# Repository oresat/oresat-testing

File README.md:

# oresat-testing
A place for all aspects of OreSat CubeSat testing

### Environmental

* Temperature (70 K to 350K) ??
* Vacuum (10ee-8 Torr)
* Vibration
* RF anechoic chamber

### RF Test equipment

* 10 MHz Rubidium Oscillator Standard
* GPS Disciplined Oscillator Standard
* Noise Source

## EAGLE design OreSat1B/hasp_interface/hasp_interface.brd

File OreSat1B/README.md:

# OreSat1B
OreSat1B is the HASP Balloon Test Payload of OreSat Subsystems to be flown on the HASP 2020 Payload round in Ft. Sumner, New Mexico.

### Tested Subsystems
- Cirrus Flux Camera
- OreSat Live
- Startracker
- C3 (Flight Computer)
- DxWiFi w/ Turnstile Antenna
- Handheld Ground Station

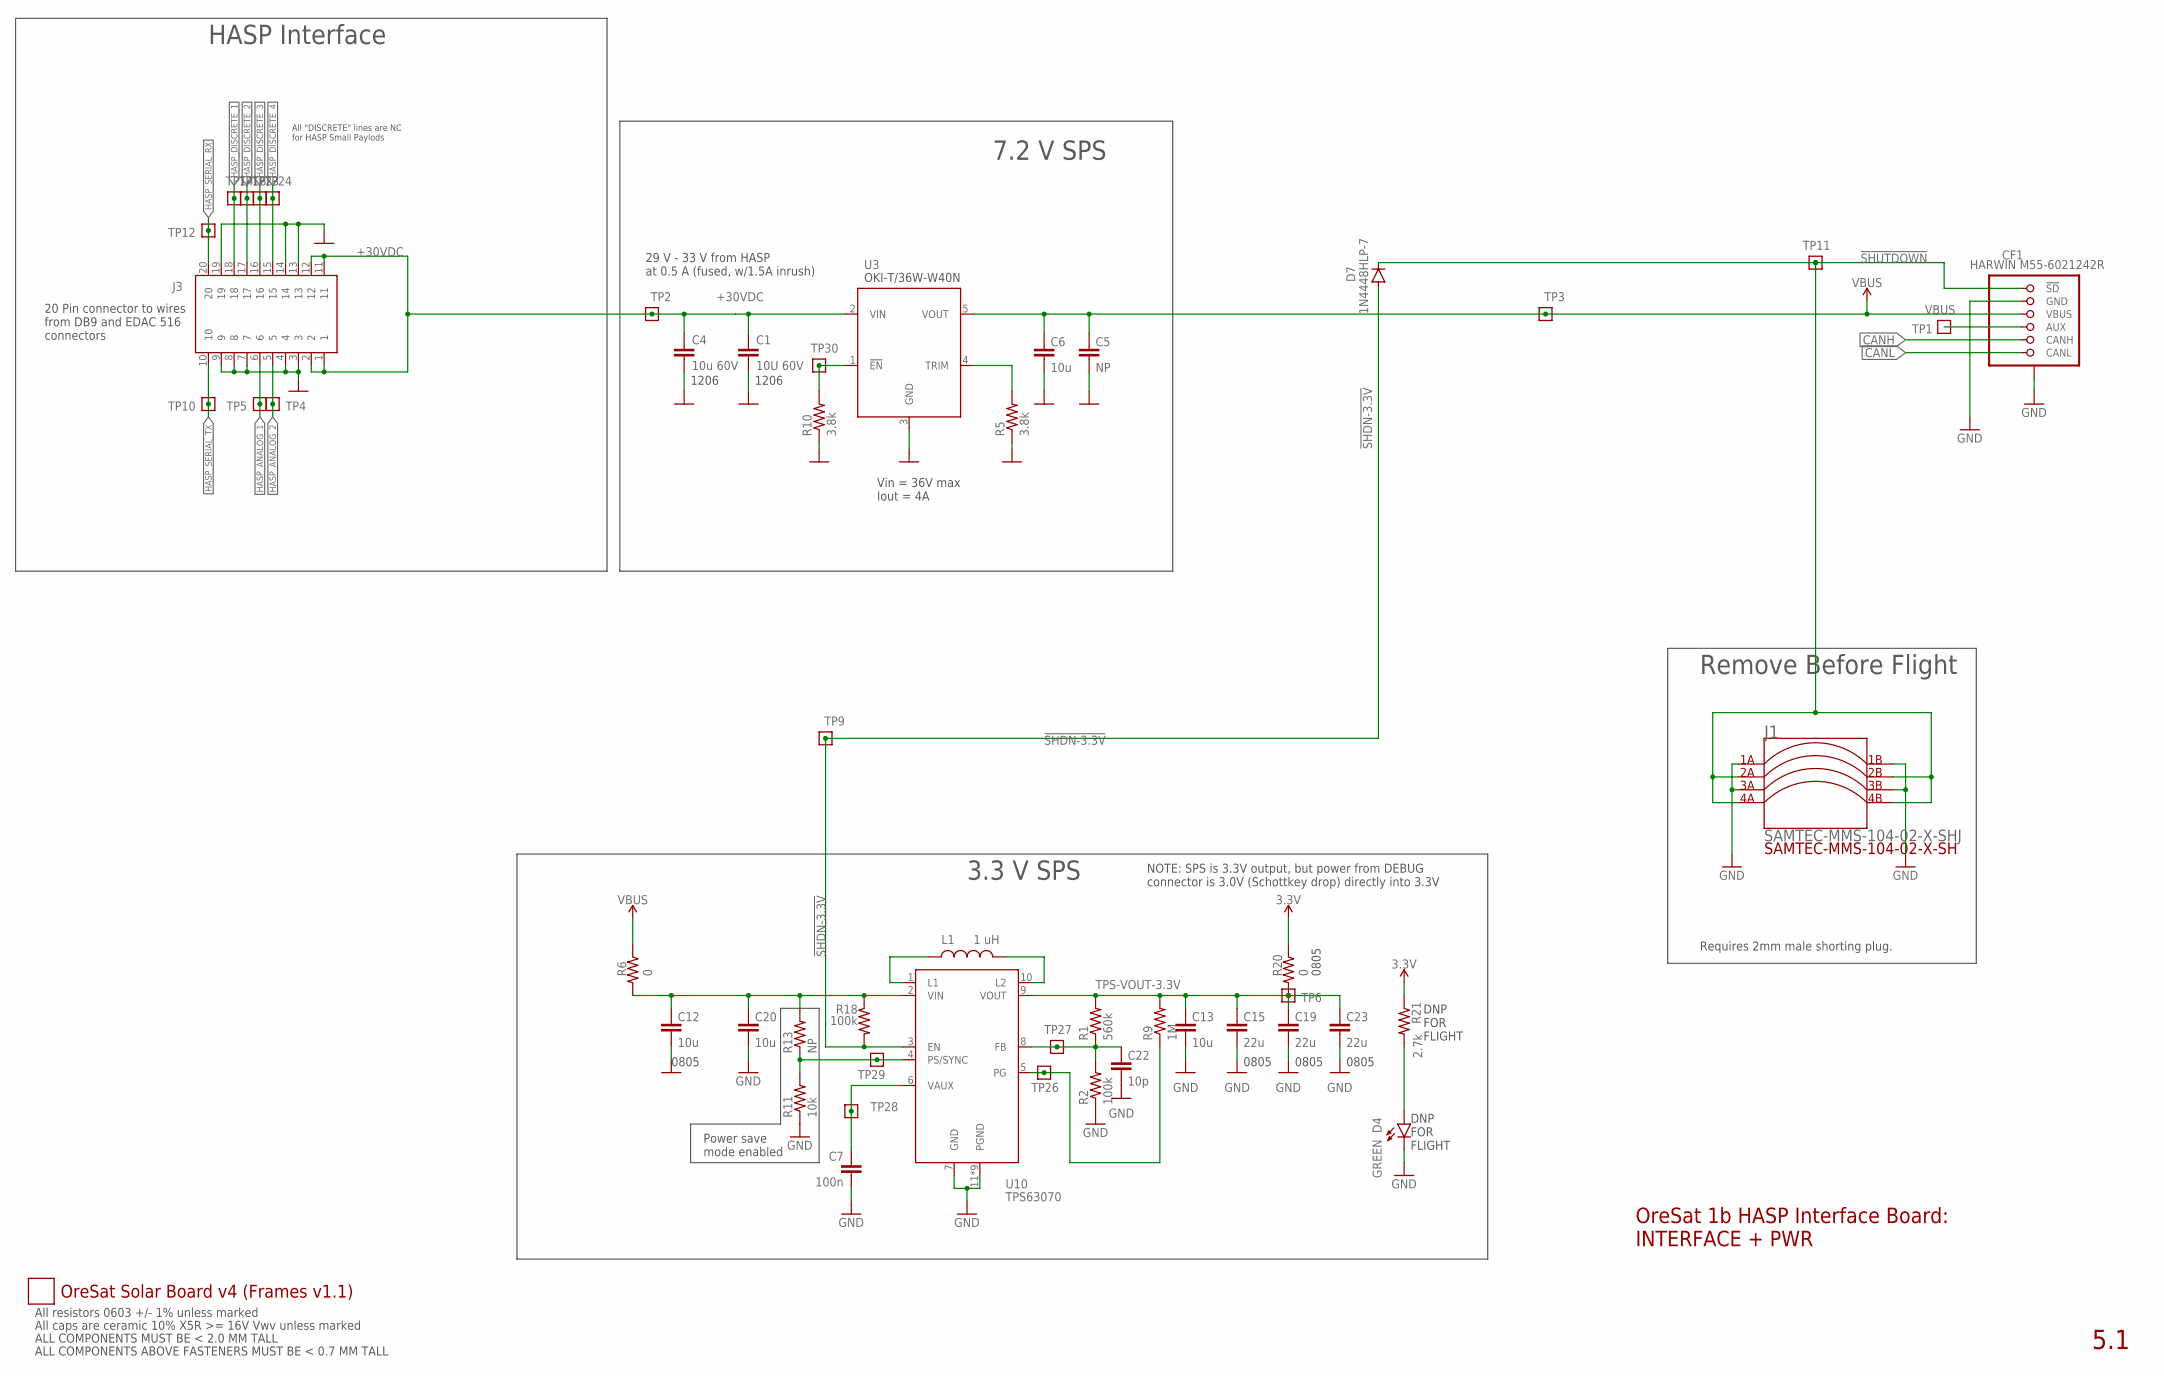
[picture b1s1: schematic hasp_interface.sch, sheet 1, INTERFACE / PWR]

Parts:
C1: 10U 60V; 1206-C
C4: 10u 60V; 1206-C
C5: NP; .0603-C-NOSILK; MPN GRT188R61C106KE13D
C6, C13, C20: 10u; .0603-C-NOSILK; MPN GRT188R61C106KE13D
C7: 100n; .0603-C-NOSILK; MPN CL10B104KB85PND
C12: 10u; .0805-B-NOSILK; MPN GRT21BR61C106KE01L
C15, C19, C23: 22u; .0805-B-NOSILK; MPN CL32B226KOJVPNE
C22: 10p; .0603-C-NOSILK; MPN GRT188R61C106KE13D
CF1: HARWIN M55-6021242R; HARWIN-M55-60X1242R
D4: GREEN; LED-0603; MPN IN-S63AT5A
D7: 1N4448HLP-7; .0402-B-NOSILK-DIODE; MPN 1N4448HLP-7
J1: SAMTEC-MMS-104-02-X-SHJ; SAMTEC-MMS-104-02-X-SH
J3: MOLEX-43045XXXXRIGHTANGLE; 0430452000
L1: 1 uH; IND_1226AS-H-1R0N=P2; MPN VLS3010CX-1R5M-1
PCB1: ORESAT-SOLAR-BOARD-V4-SPECTROLABS; ORESAT-SOLAR-BOARD-V4
R1: 560k; .0603-C-NOSILK; MPN CRGCQ0603F470K
R2: 100k; .0603-C-NOSILK; MPN RR0816P-104-D
R5, R10: 3.8k; .0603-C-NOSILK
R6, R20: 0; .0805-C-NOSILK; MPN RMCF0805ZT0R00
R9: 1M; .0603-C-NOSILK
R11: 10k; .0603-C-NOSILK
R13: NP; .0603-C-NOSILK; MPN RNCP0603FTD10K0
R18: 100k; .0603-C-NOSILK; MPN RNCP0603FTD10K0
R21: 2.7k; .0603-C-NOSILK; MPN CRGCQ0603F2K7
TP1, TP2, TP3, TP4, TP5, TP6, TP9, TP10, TP11, TP12, TP14, TP16, TP23, TP24, TP26, TP27, TP28, TP29, TP30: TEST-POINT-LARGE-SQUARE; 1X01
U3: OKI-T/36W-W40N; OKI-T/36W-W40
U10: TPS63070; CONV_TPS63060DSCT; MPN TPS63070RNMT

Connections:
3.3V: R20.1, R21.1; also elsewhere on the board
!SHDN-3.3V: D7.A, R18.2, TP9.1, U10.3 (EN)
!SHUTDOWN: CF1.1 (!SD), CF1.2 (!SD), D7.C, J1.2A, J1.2B, J1.4A, J1.4B, TP11.1
+30VDC: C1.1, C4.1, J3.1, J3.2, J3.11, J3.12, TP2.1, U3.2 (VIN)
AUX: CF1.7 (AUX), CF1.8 (AUX), TP1.1
CANH: CF1.9 (CANH), CF1.10 (CANH); also elsewhere on the board
CANL: CF1.11 (CANL), CF1.12 (CANL); also elsewhere on the board
GND: C1.2, C4.2, C5.2, C6.2, C7.2, C12.2, C13.2, C15.2, C19.2, C20.2, C22.2, C23.2, CF1.3 (GND), CF1.4 (GND), CF1.P$1 (SHIELD), CF1.P$2 (SHIELD), CF1.P$3 (SHIELD), CF1.P$4 (SHIELD), D4.C, J1.1A, J1.1B, J1.3A, J1.3B, J3.3, J3.4, J3.7, J3.8, J3.9, J3.13, J3.14, J3.19, R2.1, R5.1, R10.1, R11.1, U3.3 (GND), U10.7 (GND), U10.11 (PGND), U10.12 (PGND), U10.13 (PGND), U10.14 (PGND), U10.15 (PGND), U10.16 (PGND), U10.17 (PGND), U10.18 (PGND), U10.19 (PGND); also elsewhere on the board
HASP_ANALOG_1: J3.6, TP5.1; also elsewhere on the board
HASP_ANALOG_2: J3.5, TP4.1; also elsewhere on the board
HASP_DISCRETE_1: J3.18, TP14.1
HASP_DISCRETE_2: J3.17, TP16.1
HASP_DISCRETE_3: J3.16, TP23.1
HASP_DISCRETE_4: J3.15, TP24.1
HASP_SERIAL_RX: J3.20, TP12.1; also elsewhere on the board
HASP_SERIAL_TX: J3.10, TP10.1; also elsewhere on the board
unnamed: R5.2, U3.4 (TRIM)
unnamed: R10.2, TP30.1, U3.1 (!EN)
unnamed: D4.A, R21.2
TPS-EN: R11.2, R13.1, TP29.1, U10.4 (PS/SYNC)
TPS-FB: C22.1, R1.1, R2.2, TP27.1, U10.8 (FB)
TPS-L1: L1.1, U10.1 (L1)
TPS-L2: L1.2, U10.10 (L2)
TPS-PG: R9.1, TP26.1, U10.5 (PG)
TPS-VAUX: C7.1, TP28.1, U10.6 (VAUX)
TPS-VIN: C12.1, C20.1, R6.2, R13.2, R18.1, U10.2 (VIN)
TPS-VOUT-3.3V: C13.1, C15.1, C19.1, C23.1, R1.2, R9.2, R20.2, TP6.1, U10.9 (VOUT)
VBUS: C5.1, C6.1, CF1.5 (VBUS), CF1.6 (VBUS), R6.1, TP3.1, U3.5 (VOUT)

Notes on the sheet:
OreSat 1b HASP Interface Board: INTERFACE + PWR
5.1
All resistors 0603 +/- 1% unless marked
All caps are ceramic 10% X5R >= 16V Vwv unless marked
0805
3.3 V SPS
ALL COMPONENTS MUST BE < 2.0 MM TALL
ALL COMPONENTS ABOVE FASTENERS MUST BE < 0.7 MM TALL
NOTE: SPS is 3.3V output, but power from DEBUG connector is 3.0V (Schottkey drop) directly into 3.3V
Remove Before Flight
Requires 2mm male shorting plug.
DNP FOR FLIGHT
Power save mode enabled
HASP Interface
7.2 V SPS
29 V - 33 V from HASP at 0.5 A (fused, w/1.5A inrush)
Vin = 36V max Iout = 4A
20 Pin connector to wires from DB9 and EDAC 516 connectors
OKI-T/36W-W40N
All "DISCRETE" lines are NC for HASP Small Paylods
1206

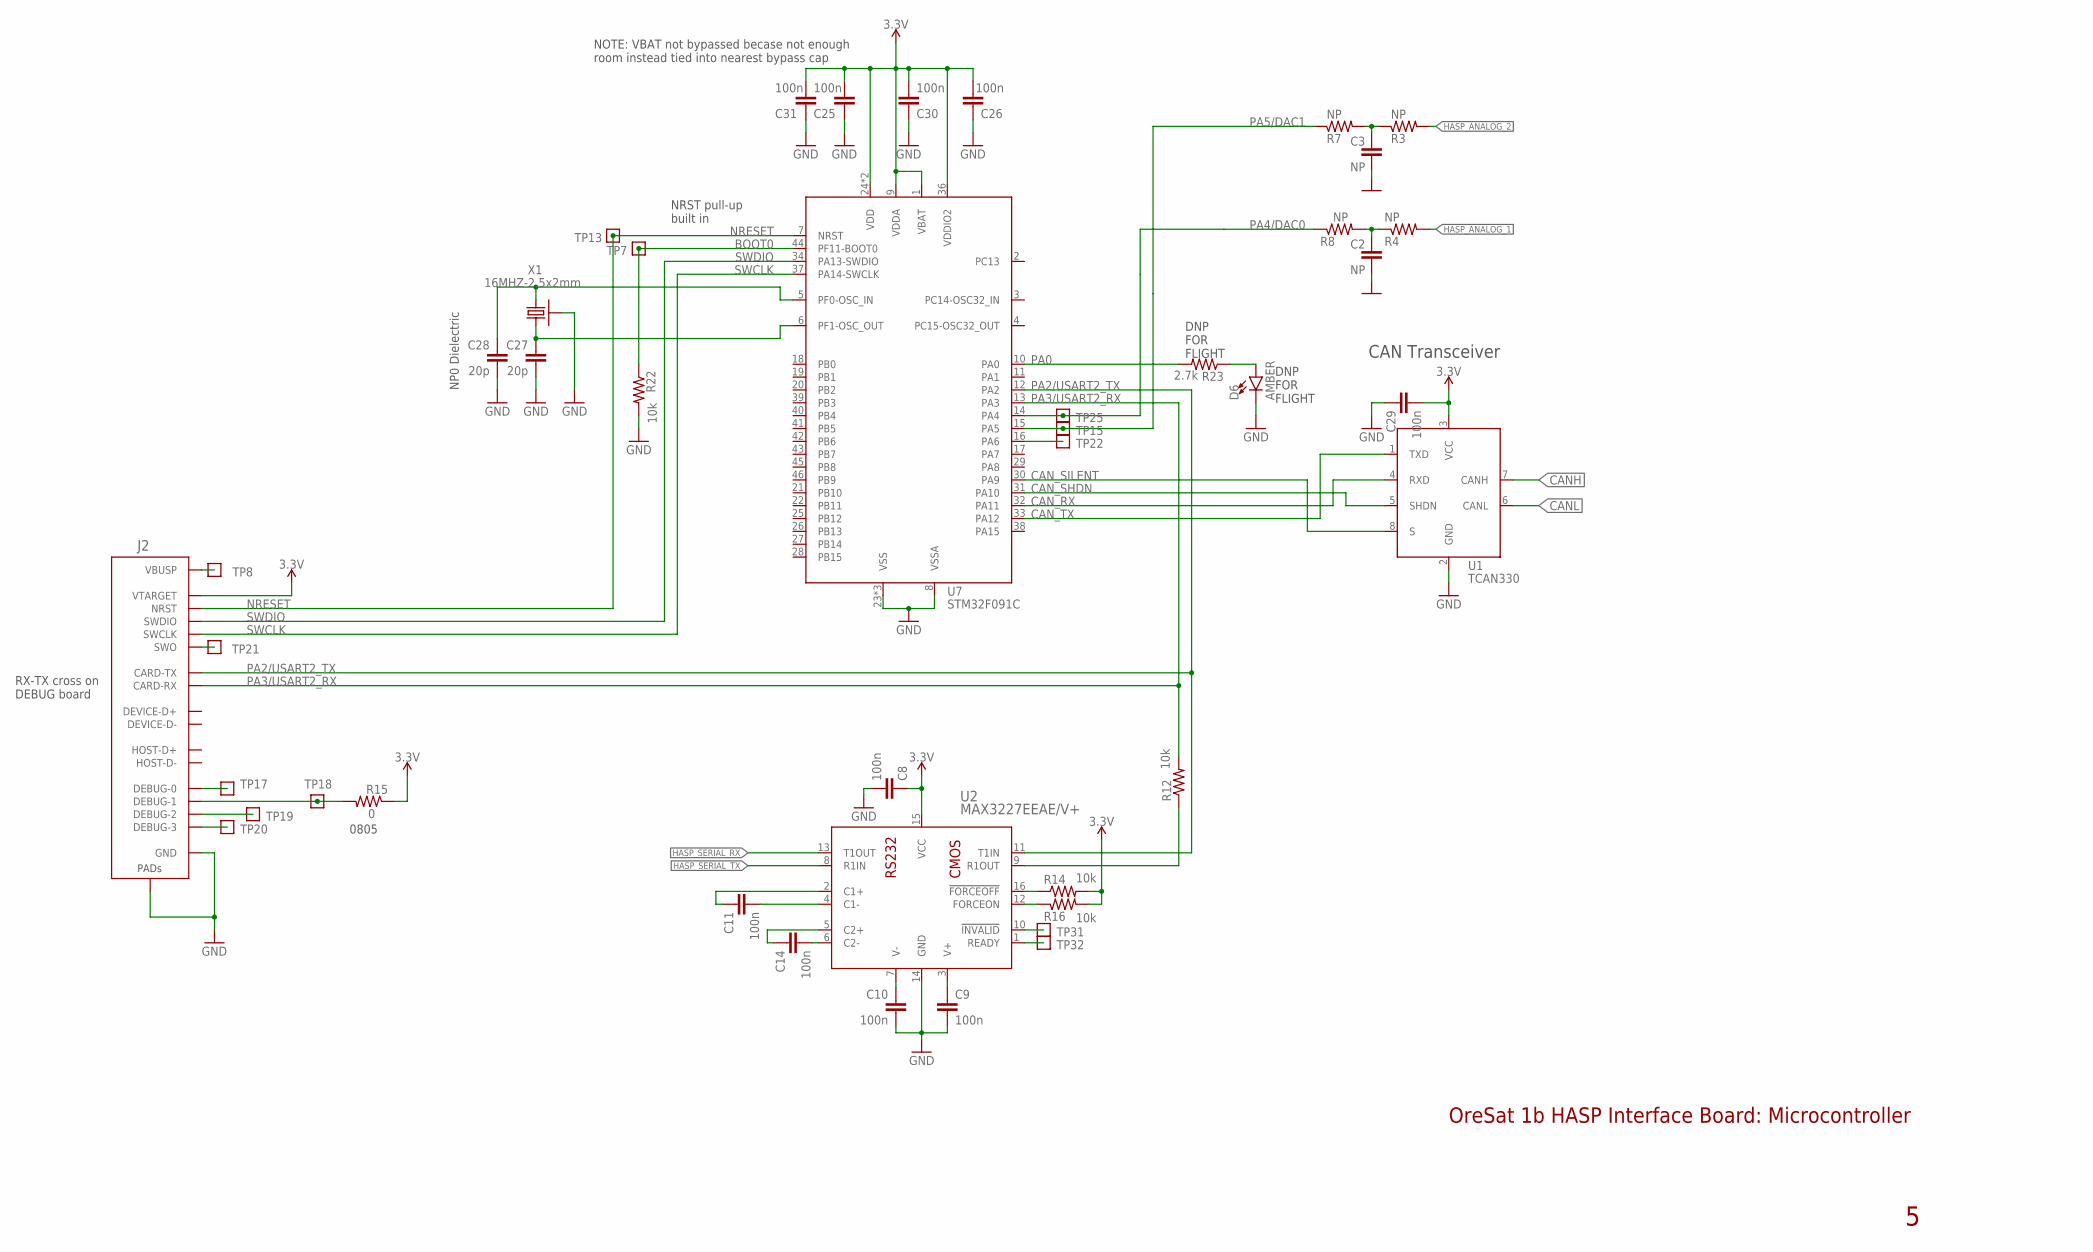
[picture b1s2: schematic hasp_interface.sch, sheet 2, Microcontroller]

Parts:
C2, C3: NP; .0603-C-NOSILK; MPN GRT188R61C106KE13D
C8, C9, C10, C11, C14, C25, C26, C29, C30, C31: 100n; .0603-C-NOSILK; MPN CL10B104KB85PND
C27, C28: 20p; .0603-C-NOSILK; MPN GCM1885C2A200JA16D
D6: AMBER; LED-0603; MPN IN-S63AT5A
J2: ORESAT-DEBUG-CONNECTOR-ALL; TE_2-1734592-0; MPN 687120183622
R3, R4, R7, R8: NP; .0603-C-NOSILK
R12, R14, R16, R22: 10k; .0603-C-NOSILK; MPN CRGCQ0603F2K7
R15: 0; .0805-C-NOSILK; MPN RMCF0805ZT0R00
R23: 2.7k; .0603-C-NOSILK; MPN CRGCQ0603F2K7
TP7, TP8, TP13, TP15, TP17, TP18, TP19, TP20, TP21, TP22, TP25, TP31, TP32: TEST-POINT-LARGE-SQUARE; 1X01
U1: TCAN330; SOT23-8_TI-DCN; MPN TCAN330GDCNT
U2: MAX3227EEAE/V+; 21-0056_A16+2_MXM
U7: STM32F091C; MPN STM32F091CCT6TR
X1: 16MHZ-2.5x2mm; CRYSTAL_2.5X2; MPN ECS-160-10-36Q-ES-TR

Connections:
3.3V: C8.1, C25.2, C26.2, C29.2, C30.2, C31.2, J2.11 (VTARGET), R14.2, R15.1, R16.2, U1.3 (VCC), U2.15 (VCC), U7.1 (VBAT), U7.9 (VDDA), U7.24 (VDD), U7.36 (VDDIO2), U7.48 (VDD); also elsewhere on the board
BOOT0: R22.1, TP7.1, U7.44 (PF11-BOOT0)
CANH: U1.7 (CANH); also elsewhere on the board
CANL: U1.6 (CANL); also elsewhere on the board
CAN_RX: U1.4 (RXD), U7.32 (PA11)
CAN_SHDN: U1.5 (SHDN), U7.31 (PA10)
CAN_SILENT: U1.8 (S), U7.30 (PA9)
CAN_TX: U1.1 (TXD), U7.33 (PA12)
DEBU-1/SOLAR3V: J2.18 (DEBUG-1), R15.2, TP18.1
DEBUG-0: J2.17 (DEBUG-0), TP17.1
DEBUG-2: J2.19 (DEBUG-2), TP19.1
DEBUG-3: J2.20 (DEBUG-3), TP20.1
GND: C2.2, C3.2, C8.2, C9.2, C10.2, C25.1, C26.1, C27.2, C28.2, C29.1, C30.1, C31.1, D6.C, J2.3 (GND), J2.6 (GND), J2.9 (GND), J2.PAD1 (PAD), J2.PAD2 (PAD), R22.2, U1.2 (GND), U2.14 (GND), U7.8 (VSSA), U7.23 (VSS), U7.35 (VSS), U7.47 (VSS), X1.2 (SHIELD), X1.4 (SHIELD); also elsewhere on the board
HASP_ANALOG_1: R4.2; also elsewhere on the board
HASP_ANALOG_2: R3.2; also elsewhere on the board
HASP_SERIAL_RX: U2.13 (T1OUT); also elsewhere on the board
HASP_SERIAL_TX: U2.8 (R1IN); also elsewhere on the board
unnamed: J2.1 (VBUSP), J2.2 (VBUSP), TP8.1
unnamed: C3.1, R3.1, R7.2
unnamed: C2.1, R4.1, R8.2
unnamed: R14.1, U2.16 (!FORCEOFF)
unnamed: C10.1, U2.7 (V-)
unnamed: C9.1, U2.3 (V+)
unnamed: C14.2, U2.6 (C2-)
unnamed: C14.1, U2.5 (C2+)
unnamed: C11.2, U2.4 (C1-)
unnamed: C11.1, U2.2 (C1+)
unnamed: R12.1, U2.9 (R1OUT)
unnamed: R16.1, U2.12 (FORCEON)
unnamed: TP31.1, U2.10 (!INVALID)
unnamed: TP32.1, U2.1 (READY)
unnamed: D6.A, R23.1
NRESET: J2.10 (NRST), TP13.1, U7.7 (NRST)
PA0: R23.2, U7.10 (PA0)
PA2/USART2_TX: J2.13 (CARD-TX), U2.11 (T1IN), U7.12 (PA2)
PA3/USART2_RX: J2.12 (CARD-RX), R12.2, U7.13 (PA3)
PA4/DAC0: R8.1, TP25.1, U7.14 (PA4)
PA5/DAC1: R7.1, TP15.1, U7.15 (PA5)
PA6: TP22.1, U7.16 (PA6)
SWCLK: J2.15 (SWCLK), U7.37 (PA14-SWCLK)
SWDIO: J2.14 (SWDIO), U7.34 (PA13-SWDIO)
SWO: J2.16 (SWO), TP21.1
XTAL1-IN: C28.1, U7.5 (PF0-OSC_IN), X1.1
XTAL1-OUT: C27.1, U7.6 (PF1-OSC_OUT), X1.3 (2)

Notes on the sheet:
NRST pull-up built in
CAN Transceiver
NOTE: VBAT not bypassed becase not enough room instead tied into nearest bypass cap
RX-TX cross on DEBUG board
NP0 Dielectric
0805
DNP FOR FLIGHT
OreSat 1b HASP Interface Board: Microcontroller

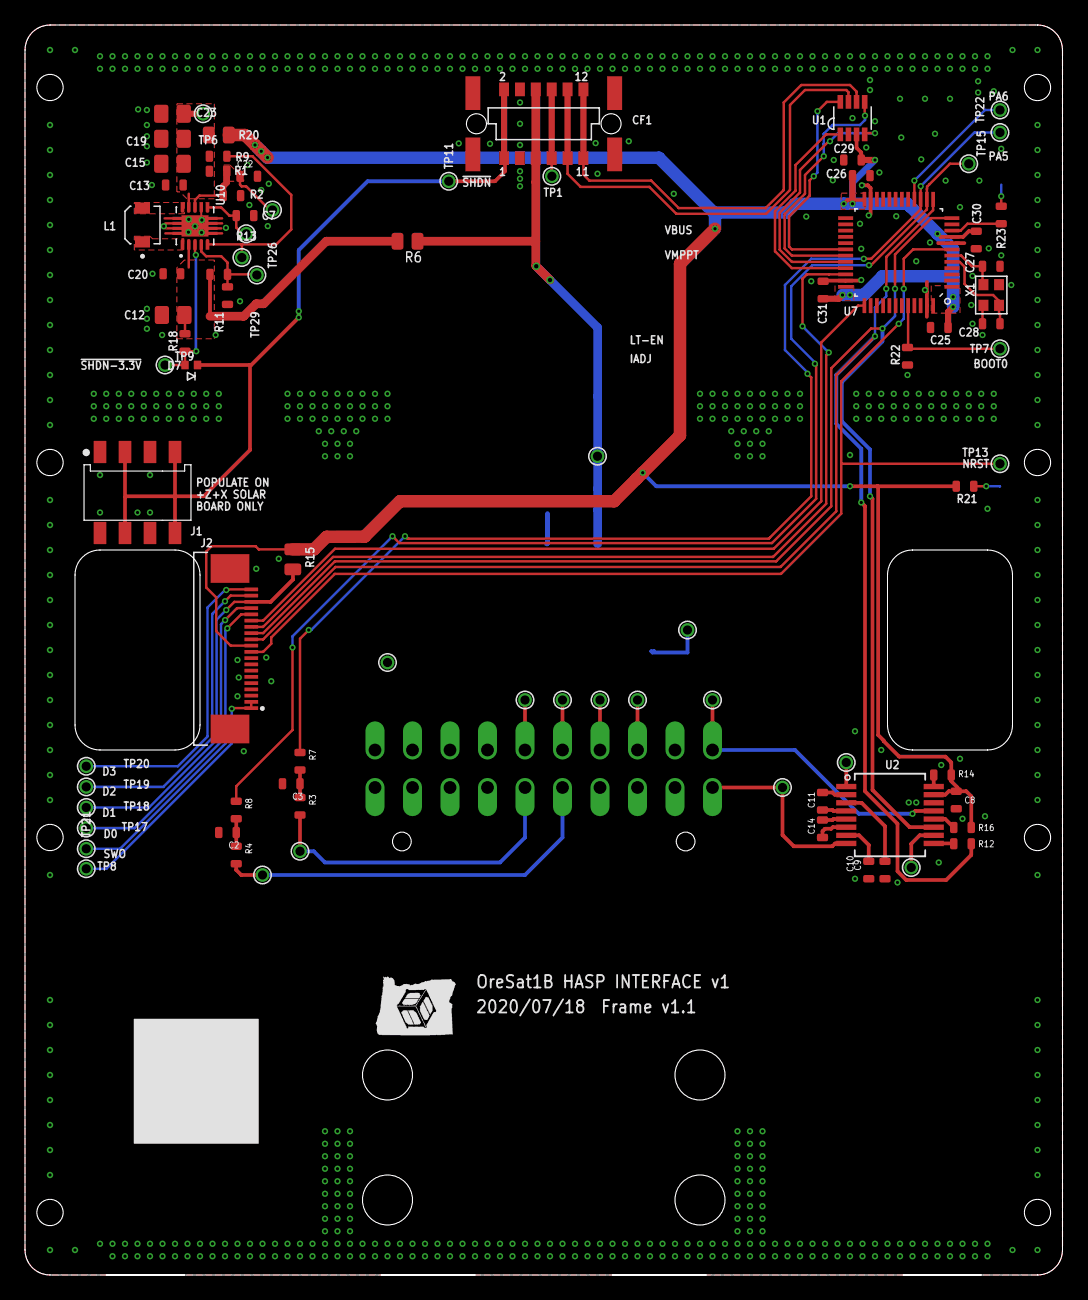
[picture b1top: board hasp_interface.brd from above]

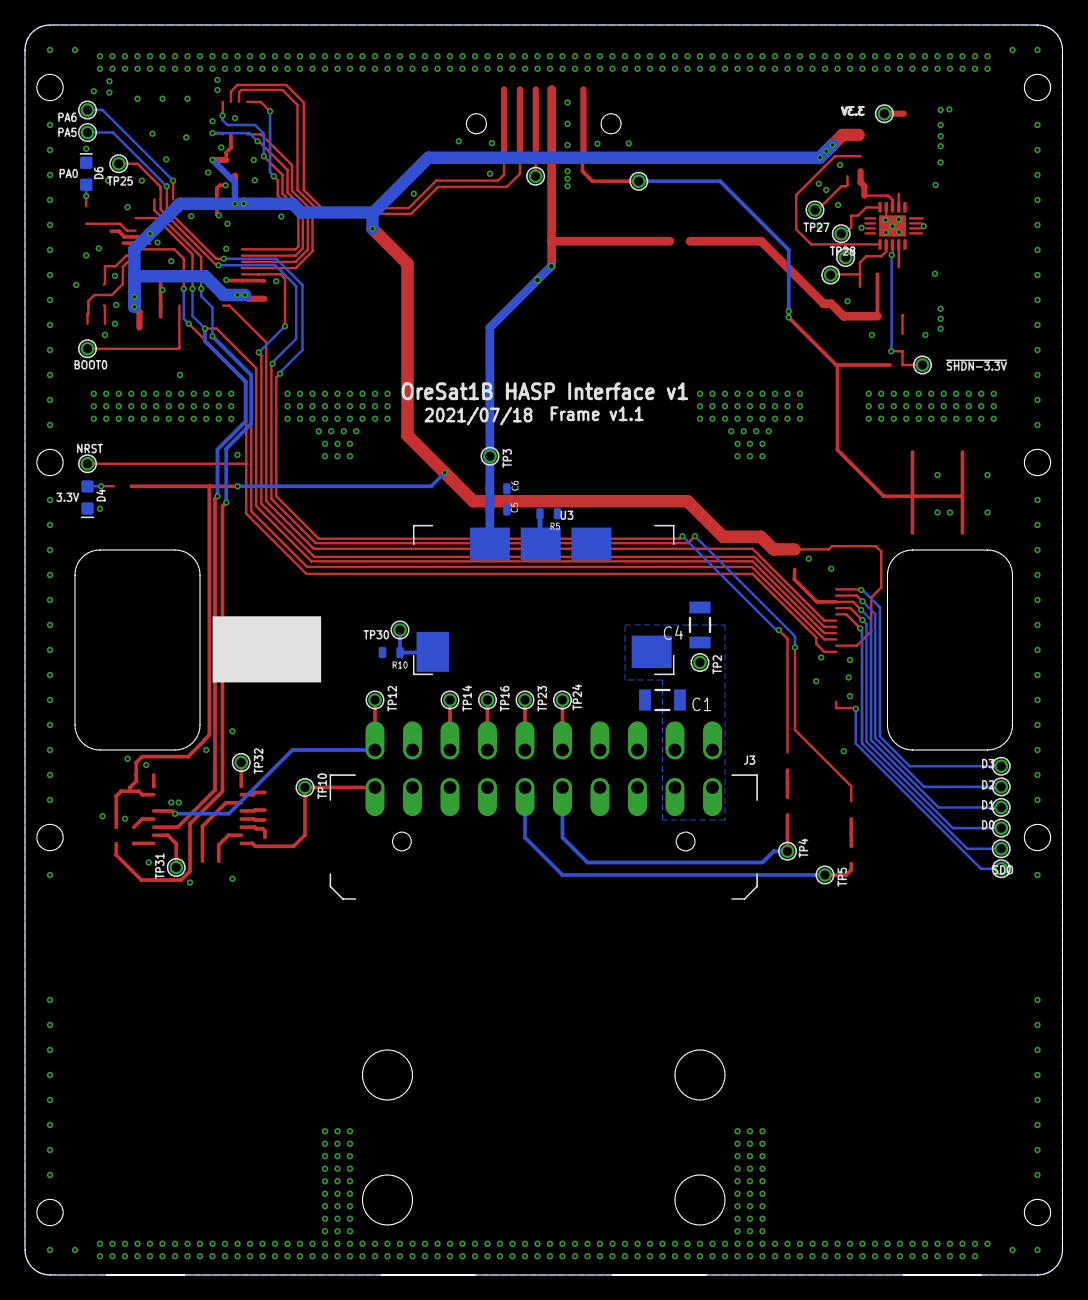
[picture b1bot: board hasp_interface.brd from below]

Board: 2 copper layers, 83.0 x 100.0 mm, 94 parts (10 on the bottom side), 64 nets.

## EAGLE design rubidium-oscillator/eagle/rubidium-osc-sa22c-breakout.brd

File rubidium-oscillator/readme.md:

### Rubidium Oscillator

This is a 10 MHz frequency standard that can be used as a reference for spectrum analyzers or
frequency counters when doing RF calibrations or confirmations of frequency.

The standard is based on a Symmetricom SA.22c Rubidium Oscillator module that is typically
used in telecom applications that need a precision frequency reference.
It's use here is intended as an atomic frequency standard that can be used in locations that
do not have easy access to a GPS constellation whereby a GPS disciplined oscillator could
provide the standard.

The Symmetricom SA.22c provides both a precision 10 MHz reference and a 1 pulse per second
timing signal. The 1 PPS signal is free runing and not syncronized to the UTC standard, such
as would be provided by the GPSDO.

Included in the repo are items used to construct the instrument starting with the
Symmetricom SA.22c atomic module.

* eagle:  Breakout board used to connect to pin header as described in table 1-1 on page 23.
* Manufacturers reference manual:
*

### Breakout Board

The SA.22c provides a Samtec 2.00 mm 2x9 socket for mating with the Samtec header [TMMH-109-01-G-DV-ES-A](https://www.samtec.com/products/tmmh-109-01-g-dv-es-a). The breakout board provides these features:

* Phoenix connectors for power (up to 14 AWG), UART, and analog in and outs (up to 20 AWG)
  * Power: 15V, 5V, and grounds
  * UART: in, out, and ground
  * Analog in: Frequency control and ground
    * 0 to 5V range for 2E-12 incremental frequency adjustment
  * Analog out: Lock and service indicators and grounds
    * Ready for driving LEDs!
    * Lock (green LED): indicates when the internal voltage controlled crystal oscillator (VCXO) is locked to the atomic transition
    * Service (red LED): indicates when internal operating parameters are near the end of their tuning or adjustment range; see pg. 30 for details
* SMA (female) connectors for RF
  * RF out: ACMOS - 10 MHz
  * 1 PPS: in and out

Note: Lock and service outputs on the SA.22c are active low.  The breakout board inverts these and is ready to drive low voltage LEDs or lamps using a [p-channel MOSFET](https://www.digikey.com/product-detail/en/diodes-incorporated/ZXMP10A13FTA/ZXMP10A13FCT-ND/560670).  Resistors R1 and R2 have been chosen to drive a 2.3V LED with 10mA.

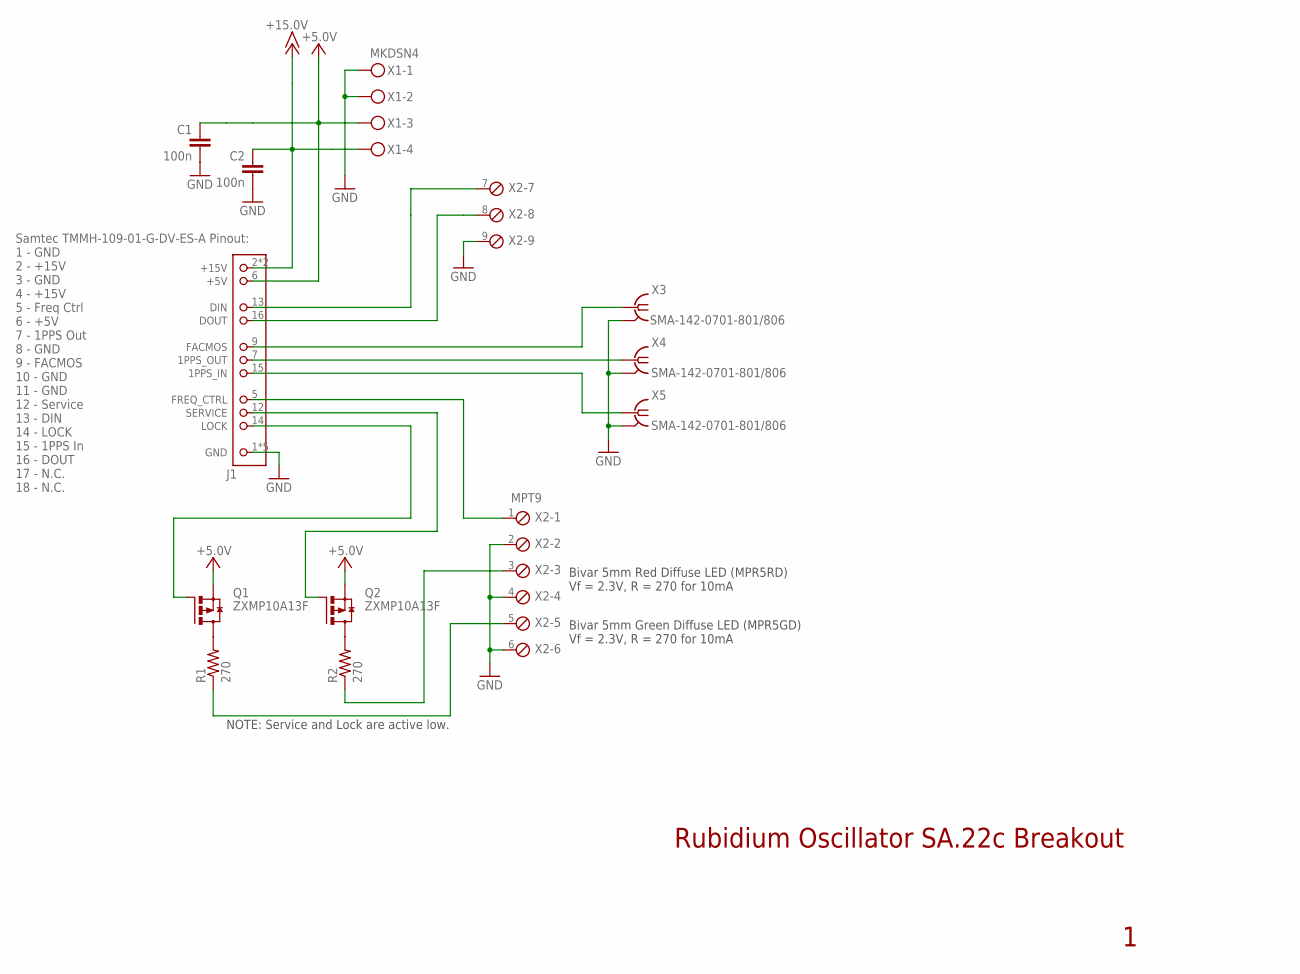
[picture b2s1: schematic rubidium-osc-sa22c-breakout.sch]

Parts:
C1, C2: 100n; C0603
J1: OSC_TMMH-109-01-G-DV-ES-A; TMMH-109-XX-XX-DV-ES-A
Q1, Q2: ZXMP10A13F; SUPER-SOT3
R1, R2: 270; R0603
X1: MKDSN4; MKDSN1,5/4-5,08
X2: MPT9; 9POL254
X3, X4, X5: SMA-142-0701-801/806; J502-ND-142-0701-801/806

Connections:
+5V: C1.1, J1.6 (+5V), Q1.2 (S), Q2.2 (S), X1.3
+15V: C2.1, J1.2 (+15V), J1.4 (+15V), X1.4
GND: C1.2, C2.2, J1.1 (GND), J1.3 (GND), J1.8 (GND), J1.10 (GND), J1.11 (GND), X1.1, X1.2, X2.2, X2.4, X2.6, X2.9, X3.G@1 (2), X3.G@2 (2), X3.G@3 (2), X3.G@4 (2), X4.G@1 (2), X4.G@2 (2), X4.G@3 (2), X4.G@4 (2), X5.G@1 (2), X5.G@2 (2), X5.G@3 (2), X5.G@4 (2)
unnamed: J1.9 (FACMOS), X3.1
unnamed: J1.7 (1PPS_OUT), X4.1
unnamed: J1.15 (1PPS_IN), X5.1
unnamed: J1.13 (DIN), X2.7
unnamed: J1.16 (DOUT), X2.8
unnamed: Q1.3 (D), R1.2
unnamed: J1.5 (FREQ_CTRL), X2.1
unnamed: J1.12 (SERVICE), Q2.1 (G)
unnamed: J1.14 (LOCK), Q1.1 (G)
unnamed: Q2.3 (D), R2.2
unnamed: R2.1, X2.3
unnamed: R1.1, X2.5

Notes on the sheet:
Rubidium Oscillator SA.22c Breakout
Bivar 5mm Green Diffuse LED (MPR5GD) Vf = 2.3V, R = 270 for 10mA
Bivar 5mm Red Diffuse LED (MPR5RD) Vf = 2.3V, R = 270 for 10mA
NOTE: Service and Lock are active low.

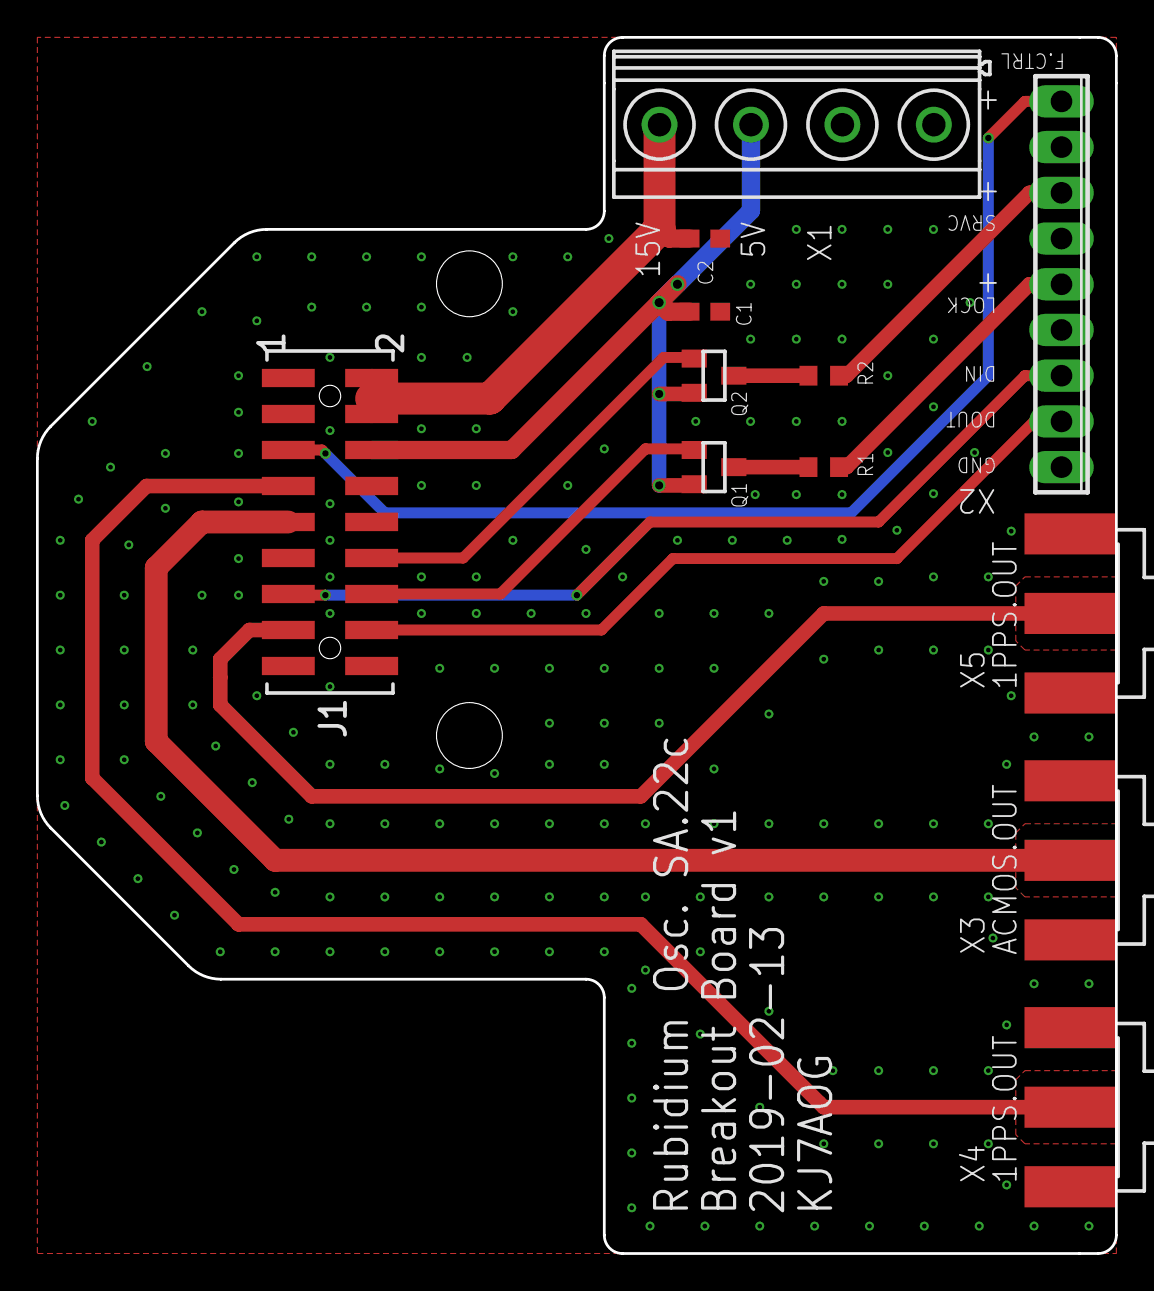
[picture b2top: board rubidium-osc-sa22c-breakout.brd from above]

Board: 2 copper layers, 59.9 x 67.6 mm, 12 parts (0 on the bottom side), 15 nets.

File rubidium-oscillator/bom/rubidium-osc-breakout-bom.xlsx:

Bill Of Materials for Rubidium Oscillator SA.22c Breakout Board
source file: rubidium-osc-sa22c-breakout.sch
Last modified: 2019-02-14
PCB version: 1 |  |  | P/DNP = | Place/Do Not Place (DNP is for final production boards)
BOM revision: 1 |  |  | Generic = | Any generic part with the same characteristics are OK (e.g., bypass cap)
Cnt | Part References | P/DNP | Mfg | Mfg PN | Description | Distributor | Dist. PN | Generic | Notes
1 | X1 | P | Phoenix Contact | 1888700 | MKDSN Fixed Terminal Block 4P 5.08mm | Mouser | 651-1888700 | N
1 | X2 | P | Phoenix Contact | 1725724 | MPT Fixed Terminal Block 9P 2.54mm | Mouser | 651-1725724 | N
3 | X3, X4, X5 | P | Johnson/Cinch | 142-0701-801 | SMA End Mount Jack, 0.062" Board | Mouser | 530-142-0701-801 | N
2 | Q1, Q2 | P | Diodes Inc. | ZXMP10A13FTA | MOSFET p-channel, SOT-23, 0.7A | Mouser | 522-ZXMP10A13FTA | Y | -3.0V typical gate threshold preferred
2 | R1, R2 | P | ROHM Semi. | ESR03EZPJ271 | 270 ohm resistor, 0603, 1/4W | Mouser | 755-ESR03EZPJ271 | Y
2 | C1, C2 | P | Yageo | CC0603JRX7R9BB104 | 100n capacitor, 0603, 50V, X7R, 5% | Mouser | 603-CC603JRX7R9BB104 | Y | >15V, 0603
1 | N/A | - | Bivar | MPR5GD | LED Panel Mount 5mm Green Diffuse | Mouser | 749-MPR5GD | Y
1 | N/A | - | Bivar | MPR5RD | LED Panel Mount 5mm Red Diffuse | Mouser | 749-MPR5RD | Y
1 | J1 | P | Samtec | TMMH-109-01-G-DV-ES-A | 2.00mm 2x9 header with shroud | - | - | N | Included with SA.22c
Revision History
Rev | Notes
1 | Initial BOM.

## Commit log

2018-04-18 Create Readme initially
    Anything I forgot?
2019-02-05 Added rubidium oscillator breakout board schematic and layout
2019-02-05 Update rubidium osc breakout layout
2019-02-05 Update README.md
    Add special RF Test equipment
2019-02-06 Updated rubidium osc. Removed thermal reliefs for SMA and power grounds. Updated p-MOSFET design.
2019-02-09 Added stitching to rub. osc. board
2019-02-09 Create readme.md
    Describe the RbOsc's purpose
2019-02-10 Added thermals, moved SMAs, updated SMA gnds, fixed board corners, fixed gnd vias
2019-02-10 Updated document
2019-02-10 Name fix
2019-02-11 Better ground vias
2019-02-12 Revamped layout
2019-02-12 Moved text to tPlace
2019-02-12 Minor tweaks
2019-02-12 SMA center pin ground clearance
2019-02-12 Adjust for proper Phoenix conn sizes.
2019-02-14 Update vias to tented and moved some, change R1 and R2 for 10mA LEDs
2019-02-14 Initial BOM
2019-02-14 Remove template tab
2019-03-26 created a solidworks file of the vacuum chamber
2019-03-26 fixed some hole sizes
2019-04-14 Fixed .gitignore file
2019-04-30 Slightly updated vacuum chamber files
2019-04-30 Updated vacuum chamber to newer model, including an assembly with DNE zones
2019-05-19 Slightly changed vacuum chamber dimensions
2019-08-20 "auto-generated from update_repos.py"
2020-01-26 added drop tower CAD and folder
2020-01-28 added readme about new CAD location for vac chamber
2020-08-31 Added TVAC fixture CAD
2020-09-08 Changed to shrouds, base assembly, mounting plate.
2020-09-08 updated shroud, added plumbing
2020-09-13 changed to shroud plumbing, added brackets
2020-09-22 changes to shrouds and base
2020-09-23 changed to shrouds and base
2020-10-07 changes to shrouds(added bevel, removed pins)
2020-10-17 changes to cryo shrouds and base
2020-10-18 added plumbing, back bracket, fasteners
2020-10-28 changes to plumbing
2020-11-15 altered top braces
2020-12-27 Inital Commit for OreSat1B
2020-12-30 Added Mounting Plate and Modified CFC Assembly
2021-01-07 Complete Redesign of OreSat1B Payload, including mounting system redesign
2021-01-08 File System Restructuring, added folder for OreSat1B specific EAGLE schematics
2021-02-26 Preliinary HASP interface PCB Schematic.
2021-02-26 Cleanup on HASP interface board
2021-04-04 Create contents
2021-04-22 Drop tower 3U configurations
2021-04-27 Drop-tower
2021-04-30 drop tower
2021-05-16 Wire cleanup
2021-05-16 Removed temporary files, changed .gitignore.
2021-05-18 Updated schematic
2021-05-18 Cleaned up and fixed errors on 30V SPS, removed some old solar module cruft.
2021-07-10 Added new cots dc dc converter and updated HASP interface connection.
2021-07-16 Updated connector footprint and did layout
2021-07-18 Added RS232 level converter in case we want it. Added DAC outputs to HASP analog inputs in case we want it. Moved main connector out of fastener's way. Cleanup.
2021-07-20 Added HASP interface BOM
2022-05-01 Helper scripts for EDL tests to an airplane
2022-05-02 Mid-flight retooling for Mode-S transponder
2022-05-02 Initial commit of recorded data
2022-05-02 Added location and received beacon information from CessnaSat
2022-05-29 HelmholtzCage

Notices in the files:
parts and their libraries:
SparkFun-LED: Licensing: Creative Commons ShareAlike 4.0 International - https://creativecommons.org/licenses/by-sa/4.0
